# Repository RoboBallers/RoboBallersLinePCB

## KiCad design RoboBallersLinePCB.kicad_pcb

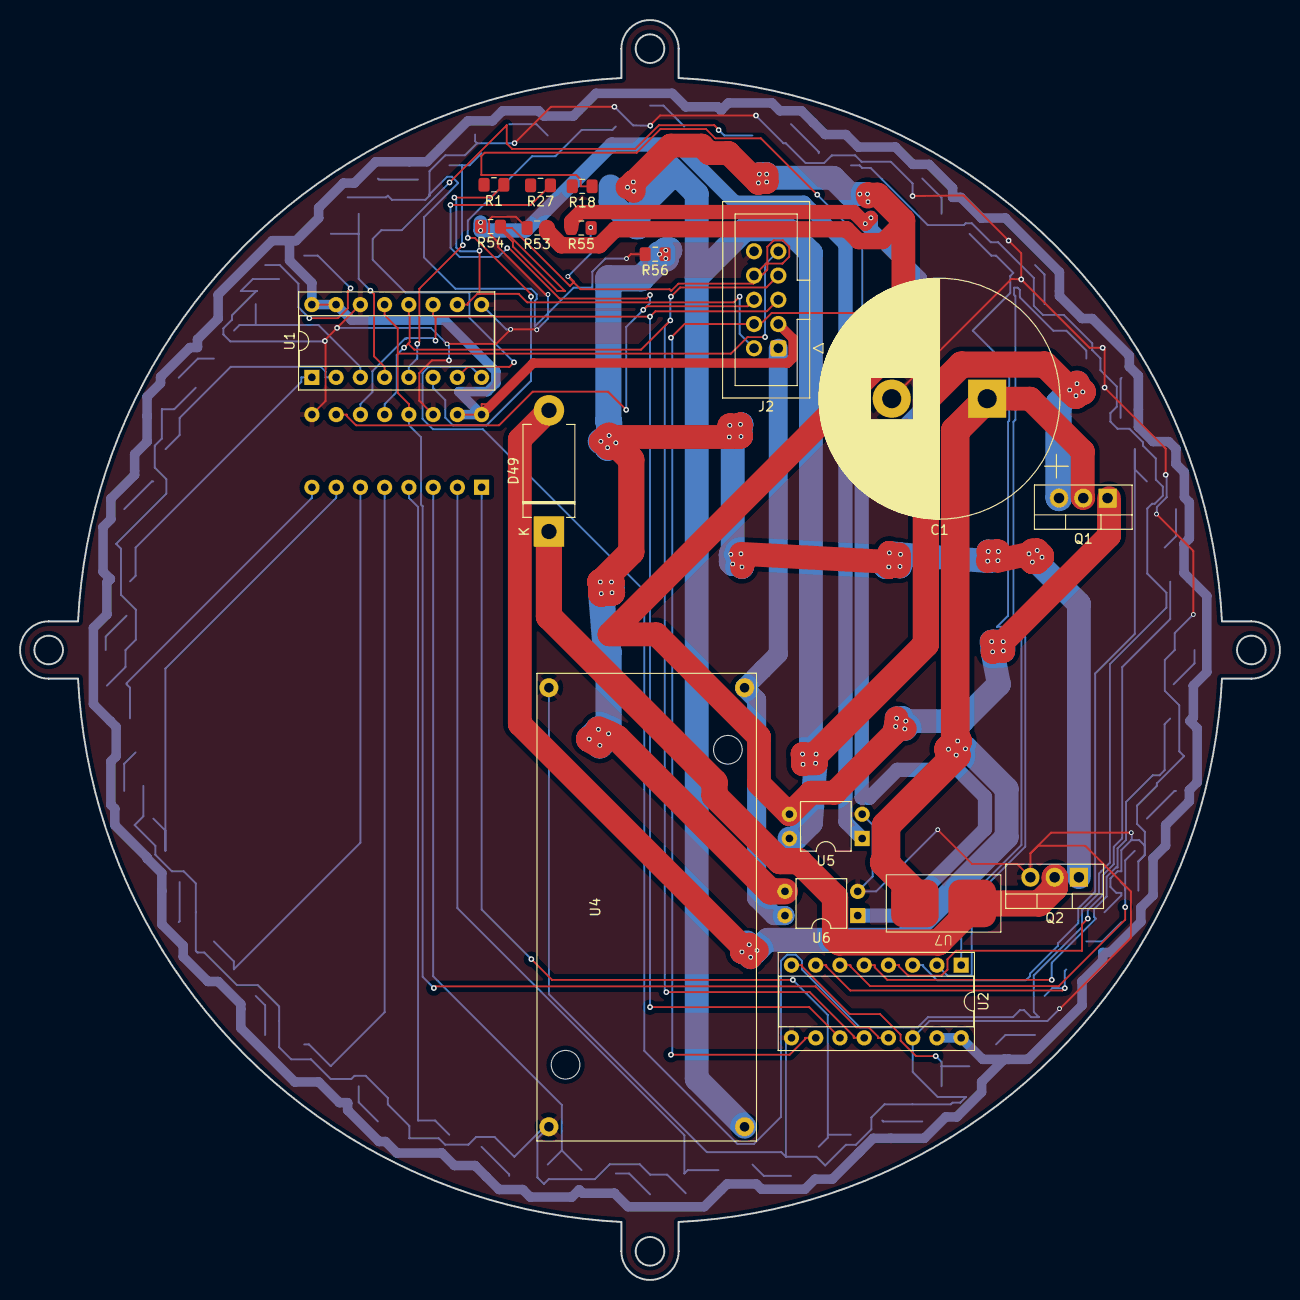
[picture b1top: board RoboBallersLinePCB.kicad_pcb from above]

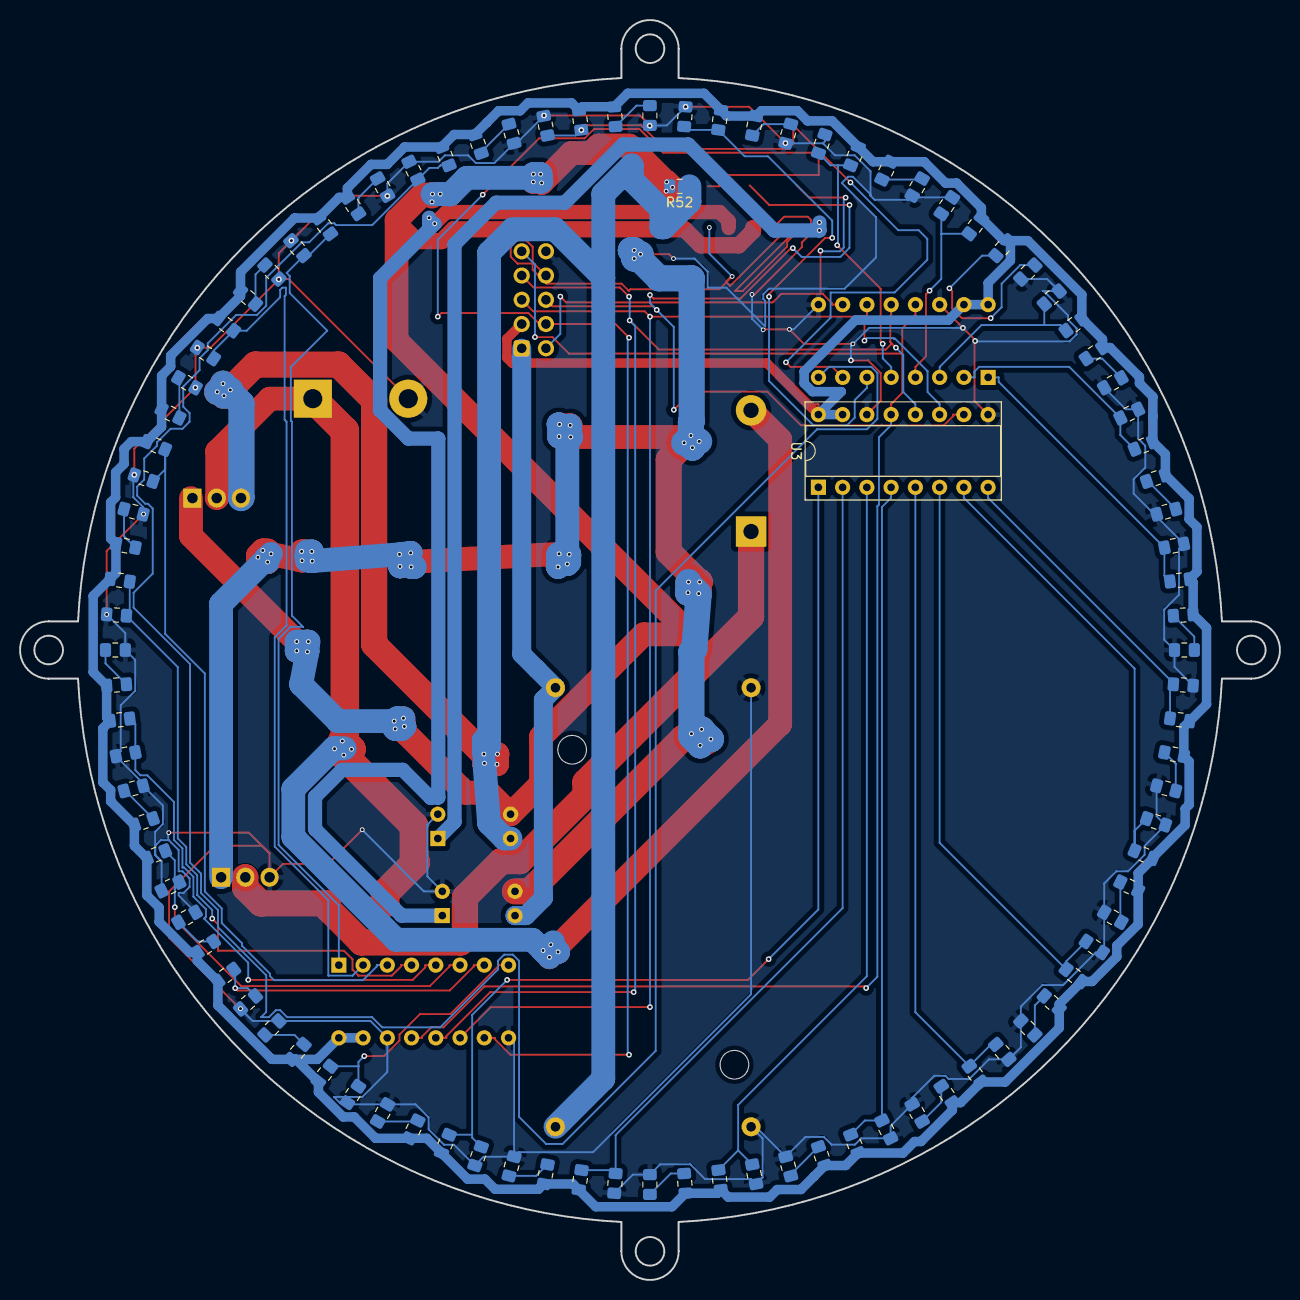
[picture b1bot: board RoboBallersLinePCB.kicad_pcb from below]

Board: 2 copper layers, 132.0 x 132.0 mm, 116 parts (98 on the bottom side), 65 nets.

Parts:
C1: 80v 2200uf; CP_Radial_D25.0mm_P10.00mm_SnapIn
D1, D2, D3, D4, D5, D6, D7, D8, D9, D10, D11, D12, D13, D14, D15, D16, D17, D18, D19, D20, D21, D22, D23, D24: LED; C_0805_2012Metric_Pad1.18x1.45mm_HandSolder
D25, D26, D27, D28, D29, D30, D31, D32, D33, D34, D35, D36, D37, D38, D39, D40, D41, D42, D43, D44, D45, D46, D47, D48: D_Photo; C_0805_2012Metric_Pad1.18x1.45mm_HandSolder
D49: Diode; D_DO-201AD_P12.70mm_Horizontal
J2: Bottom PCB; IDC-Header_2x05_P2.54mm_Vertical
Q1: P-Channel; TO-220-3_Vertical
Q2: N-Channel; TO-220-3_Vertical
R1, R18, R27, R56: 10k; C_0805_2012Metric_Pad1.18x1.45mm_HandSolder
R2, R3, R4, R5, R6, R7, R8, R9, R10, R11, R12, R13, R14, R15, R16, R17, R19, R20, R21, R22, R23, R24, R25, R26: 750; C_0805_2012Metric_Pad1.18x1.45mm_HandSolder
R28, R29, R30, R31, R32, R33, R34, R35, R36, R37, R38, R39, R40, R41, R42, R43, R44, R45, R46, R47, R48, R49, R50, R51: 14k; C_0805_2012Metric_Pad1.18x1.45mm_HandSolder
R52: 5k; C_0805_2012Metric_Pad1.18x1.45mm_HandSolder
R53: 19k; C_0805_2012Metric_Pad1.18x1.45mm_HandSolder
R54, R55: 210; C_0805_2012Metric_Pad1.18x1.45mm_HandSolder
U1, U2, U3: MCP3008; DIP-16_W7.62mm_Socket
U4: BoostConverter; Boost_Convertor_LM2577
U5, U6: NSL-32; DIP-4_W7.62mm
U7: Solenoid-Electric; KickerPad

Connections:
3.3v: D25.2 (A), D26.2 (A), D27.2 (A), D28.2 (A), D29.2 (A), D30.2 (A), D31.2 (A), D32.2 (A), D33.2 (A), D34.2 (A), D35.2 (A), D36.2 (A), D37.2 (A), D38.2 (A), D39.2 (A), D40.2 (A), D41.2 (A), D42.2 (A), D43.2 (A), D44.2 (A), D45.2 (A), D46.2 (A), D47.2 (A), D48.2 (A), J2.3, R2.2, R3.2, R4.2, R5.2, R6.2, R7.2, R8.2, R9.2, R10.2, R11.2, R12.2, R13.2, R14.2, R15.2, R16.2, R17.2, R19.2, R20.2, R21.2, R22.2, R23.2, R24.2, R25.2, R26.2, U1.15 (Vref), U1.16 (Vdd), U2.15 (Vref), U2.16 (Vdd), U3.15 (Vref), U3.16 (Vdd)
12v: J2.1, U4.1 (In+), U6.4 (R)
48v: Q1.3 (S), R52.1, U4.3 (Out+), U5.4 (R)
CH01: D25.1 (K), R28.1, U1.1 (CH0)
CH02: D33.1 (K), R36.1, U2.1 (CH0)
CH03: D41.1 (K), R44.1, U3.1 (CH0)
CH11: D26.1 (K), R29.1, U1.2 (CH1)
CH12: D34.1 (K), R37.1, U2.2 (CH1)
CH13: D42.1 (K), R45.1, U3.2 (CH1)
CH21: D27.1 (K), R30.1, U1.3 (CH2)
CH22: D35.1 (K), R38.1, U2.3 (CH2)
CH23: D43.1 (K), R46.1, U3.3 (CH2)
CH31: D28.1 (K), R31.1, U1.4 (CH3)
CH32: D36.1 (K), R39.1, U2.4 (CH3)
CH33: D44.1 (K), R47.1, U3.4 (CH3)
CH41: D29.1 (K), R32.1, U1.5 (CH4)
CH42: D37.1 (K), R40.1, U2.5 (CH4)
CH43: D45.1 (K), R48.1, U3.5 (CH4)
CH51: D30.1 (K), R33.1, U1.6 (CH5)
CH52: D38.1 (K), R41.1, U2.6 (CH5)
CH53: D46.1 (K), R49.1, U3.6 (CH5)
CH61: D31.1 (K), R34.1, U1.7 (CH6)
CH62: D39.1 (K), R42.1, U2.7 (CH6)
CH63: D47.1 (K), R50.1, U3.7 (CH6)
CH71: D32.1 (K), R35.1, U1.8 (CH7)
CH72: D40.1 (K), R43.1, U2.8 (CH7)
CH73: D48.1 (K), R51.1, U3.8 (CH7)
CSLS1: J2.2, R1.1, U1.10 (~CS/SHDN)
CSLS2: J2.4, R18.1, U2.10 (~CS/SHDN)
CSLS3: J2.6, R27.1, U3.10 (~CS/SHDN)
GND: C1.2, D1.1 (K), D2.1 (K), D3.1 (K), D4.1 (K), D5.1 (K), D6.1 (K), D7.1 (K), D8.1 (K), D9.1 (K), D10.1 (K), D11.1 (K), D12.1 (K), D13.1 (K), D14.1 (K), D15.1 (K), D16.1 (K), D17.1 (K), D18.1 (K), D19.1 (K), D20.1 (K), D21.1 (K), D22.1 (K), D23.1 (K), D24.1 (K), J2.10, Q2.3 (S), R28.2, R29.2, R30.2, R31.2, R32.2, R33.2, R34.2, R35.2, R36.2, R37.2, R38.2, R39.2, R40.2, R41.2, R42.2, R43.2, R44.2, R45.2, R46.2, R47.2, R48.2, R49.2, R50.2, R51.2, R53.2, R56.2, U1.9 (DGND), U1.14 (AGND), U2.9 (DGND), U2.14 (AGND), U3.9 (DGND), U3.14 (AGND), U4.2 (In-), U4.4 (Out-), U5.2 (K), U6.2 (K)
Kicker: J2.8, R54.1, R55.1
MISO: J2.7, U1.12 (Dout), U2.12 (Dout), U3.12 (Dout)
MOSI: J2.5, U1.11 (Din), U2.11 (Din), U3.11 (Din)
unnamed: D1.2 (A), R2.1
unnamed: D2.2 (A), R3.1
unnamed: D3.2 (A), R4.1
unnamed: D4.2 (A), R5.1
unnamed: D5.2 (A), R6.1
unnamed: D6.2 (A), R7.1
unnamed: D7.2 (A), R8.1
unnamed: D8.2 (A), R9.1
unnamed: D9.2 (A), R10.1
unnamed: D10.2 (A), R11.1
unnamed: D11.2 (A), R12.1
unnamed: D12.2 (A), R13.1
unnamed: D13.2 (A), R14.1
unnamed: D14.2 (A), R15.1
unnamed: D15.2 (A), R16.1
unnamed: D16.2 (A), R17.1
unnamed: D17.2 (A), R19.1
unnamed: D18.2 (A), R20.1
unnamed: D19.2 (A), R21.1
unnamed: D20.2 (A), R22.1
unnamed: D21.2 (A), R23.1
unnamed: D22.2 (A), R24.1
unnamed: D23.2 (A), R25.1
unnamed: D24.2 (A), R26.1
unnamed: D49.1 (A), Q2.2 (D), U7.2 (GND)
unnamed: C1.1, D49.2 (K), Q1.2 (D), U7.1 (VCC)
unnamed: Q1.1 (G), R52.2, R53.1, U5.3 (R)
unnamed: Q2.1 (G), R56.1, U6.3 (R)
unnamed: R54.2, U5.1 (A)
unnamed: R55.2, U6.1 (A)
SCK1: J2.9, U1.13 (CLK), U2.13 (CLK), U3.13 (CLK)

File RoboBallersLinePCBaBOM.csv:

"Reference","Value","Datasheet","Footprint","Qty","DNP"
"C1","80v 2200uf","~","Capacitor_THT:CP_Radial_D25.0mm_P10.00mm_SnapIn","1",""
"D1,D2,D3,D4,D5,D6,D7,D8,D9,D10,D11,D12,D13,D14,D15,D16,D17,D18,D19,D20,D21,D22,D23,D24","LED","~","Capacitor_SMD:C_0805_2012Metric_Pad1.18x1.45mm_HandSolder","24",""
"D25,D26,D27,D28,D29,D30,D31,D32,D33,D34,D35,D36,D37,D38,D39,D40,D41,D42,D43,D44,D45,D46,D47,D48","D_Photo","~","Capacitor_SMD:C_0805_2012Metric_Pad1.18x1.45mm_HandSolder","24",""
"D49","Diode","~","Diode_THT:D_DO-201AD_P12.70mm_Horizontal","1",""
"J1","Conn_01x04","~","Connector_PinHeader_2.54mm:PinHeader_1x04_P2.54mm_Vertical","1",""
"J2","Bottom PCB","http://suddendocs.samtec.com/prints/ftsh-1xx-xx-xxx-dv-xxx-x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","Connector_IDC:IDC-Header_2x05_P2.54mm_Vertical","1",""
"Q1","P-Channel","https://www.infineon.com/dgdl/Infineon-BSP89-DS-v02_02-en.pd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","Package_TO_SOT_THT:TO-220-3_Vertical","1",""
"Q2","N-Channel","https://www.vishay.com/docs/62843/sud08p06-155l-ge3.pdf","Package_TO_SOT_THT:TO-220-3_Vertical","1",""
"R1,R18,R27,R56","10k","~","Capacitor_SMD:C_0805_2012Metric_Pad1.18x1.45mm_HandSolder","4",""
"R2,R3,R4,R5,R6,R8,R9,R10,R11,R12,R13,R14,R15,R16,R17,R19,R20,R21,R22,R23,R24,R25,R26","750","~","Capacitor_SMD:C_0805_2012Metric_Pad1.18x1.45mm_HandSolder","23",""
"R7","165","~","Capacitor_SMD:C_0805_2012Metric_Pad1.18x1.45mm_HandSolder","1",""
"R28,R29,R30,R31,R32,R33,R34,R35,R36,R37,R38,R39,R40,R41,R42,R43,R44,R45,R46,R47,R48,R49,R50,R51","14k","~","Capacitor_SMD:C_0805_2012Metric_Pad1.18x1.45mm_HandSolder","24",""
"R52","5k","~","Capacitor_SMD:C_0805_2012Metric_Pad1.18x1.45mm_HandSolder","1",""
"R53","19k","~","Capacitor_SMD:C_0805_2012Metric_Pad1.18x1.45mm_HandSolder","1",""
"R54,R55","210","~","Capacitor_SMD:C_0805_2012Metric_Pad1.18x1.45mm_HandSolder","2",""
"U1,U2,U3","MCP3008","http://ww1.microchip.com/downloads/en/DeviceDoc/21295d.pdf","Package_DIP:DIP-16_W7.62mm_Socket","3",""
"U4","BoostConverter","","BoostConverter:Boost_Convertor_LM2577","1",""
"U5,U6","NSL-32","http://lunainc.com/wp-content/uploads/2016/06/NSL-32.pdf","Package_DIP:DIP-4_W7.62mm","2",""
"U7","Solenoid-Electric","","KickerPad:KickerPad","1",""

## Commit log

2024-11-15 Footprints assigned
2024-11-17 added stuff
2024-11-17 GOATED
2024-11-17 PCB + Footprint Revisions
2024-11-17 Idk if the changes didnt save
    Correct version is this one or something else
2024-11-17 More PCB Stuff
2024-11-20 Added components to new layout of pcb
2024-11-21 LinePCB Manual Traces done
2024-11-21 good stuff
2024-11-21 Added Vias, board done
    - Need to fix outline errors
    - Need to look at other errors, are they important?
2024-11-26 Changed One Via
2024-11-30 stoopid 0.2mm -> 1 mm
    - Fixed 90 errors, now realized need to change traces from 0.2mm to 1 mm
2024-11-30 I am better than Spem
    - He coulndt do 3.3v
    HAAHAHAHAHHA
    I AM BETTER
2024-11-30 spem needs to try
2024-11-30 PREMM I FIXED ITTT
2024-12-02 i think it worked
2024-12-02 wait yes it worked
2024-12-03 prem really did not cook so i had to cook
2024-12-10 nicve
2024-12-12 redid whole pcb
